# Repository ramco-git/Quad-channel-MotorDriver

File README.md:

# クアッドチャンネルモータードライバ (超はんだもりもり森鴎外!）

クアッドチャネルのDCブラシ付きモータードライバ基板です。内臓MCUにSTM32F405RGT6を使用し、4つのエンコーダ入力と1つのUART、1つのclassic CANに対応しています。内部でのPID制御が可能です。エンコーダはインクリメンタル式にのみ対応し、ゼロ校正に必要なZ相を引き出しています。すべての通信線は5Vトレラントピンに接続されています。入力信号をダイオードによりミックスしているため、内部から、又は外部から直接PWMとDIR信号を入力して動作させることができます。

## 仕様
・MCUにSTM32F405RGT6を使用し、回転数、位置制御を基板単体で可能です。
| 機能 | 個数 | 備考 |
|-:|-|-|
| モータードライバ | 4 | 30V、連続10A(なお性能試験を行っていないため、詳細は不明) |
| モーター出力 | 4 | XT60PW-F |
| 電源入力 | 1 | XT60PW-M |
|　MCU | 1 | STM32F405RGT6 |
| ユーザーLED | 1 | RGBの一体型チップ |
| ユーザーボタン | 1 | CANのID設定などに使用 |

## 信号線、マイコンのピンアサイン、コネクタの種類、番号
 
| 機能 | ピン | コネクタ種類 | パッドナンバー | 備考 |
|-:|-|-|-|-|
| CAN | TX(PB9) RX(PB8) | S04B-XASK-1,B04B-XASK-1 | J18,J19 | 
| UART | TX(PB10) RX(PB11) | DF1BZ-4P-2.5DSA | J6 |
| エンコーダ-1 | A(PA8) B(PA9) Z(PC0) | S05B-PASK-2 | J1 | TIM1 |
| エンコーダ-2 | A(PA0) B(PA1) Z(PC1) | S05B-PASK-2 | J2 | TIM2 |
| エンコーダ-3 | A(PA6) B(PA7) Z(PC2) | S05B-PASK-2 | J3 | TIM3 |
| エンコーダ-4 | A(PB6) B(PB7) Z(PC3) | S05B-PASK-2 | J4 | TIM4 |
| PWM-1(内臓MCUから) | PWM(PC6) DIR(PB12) | - | - | TIM8-CH1 |
| PWM-2(内臓MCUから) | PWM(PC7) DIR(PB13) | - | - | TIM8-CH2 |
| PWM-3(内臓MCUから) | PWM(PC8) DIR(PA10) | - | - | TIM8-CH3 |
| PWM-4(内臓MCUから) | PWM(PC9) DIR(PA11) | - | - | TIM8-CH4 |
| PWM-1(外部入力から) | DIR(1ピン) PWM(2ピン) GND(3ピン) | B03B-XASK-1 | J14 | - |
| PWM-2(外部入力から) | DIR(1ピン) PWM(2ピン) GND(3ピン) | B03B-XASK-1 | J15 | - |
| PWM-3(外部入力から) | DIR(1ピン) PWM(2ピン) GND(3ピン) | B03B-XASK-1 | J16 | - |
| PWM-4(外部入力から) | DIR(1ピン) PWM(2ピン) GND(3ピン) | B03B-XASK-1 | J17 | - |
| マイコン電源入力 | 12V(未使用,1ピン) 5V(2ピン) GND(3ピン) | B3B-XH-A | J7 | - |
| ユーザーLED | 赤(PB14) 緑(PA3) 青(PB15) | | D2 | TIMに接続されている |
| ユーザーボタン | (PC15) | - | SW2 | - | マイコン側でプルアップする |

## 内部ファームウェア
・現在調整中です。しばらくお待ちください。

## 名前の由来
大電流に対応させるため、銅線をバスバーとして使用した。その結果、基板がはんだだらけになってしまった。「超」はんだもりもり森鷗外!が誕生した。

## 以前の問題
・PWM,DIR信号ミックスに使用したBAT54CTのフットプリントのサイズミス
・部品番号の煩雑性

公開版では改善されています。

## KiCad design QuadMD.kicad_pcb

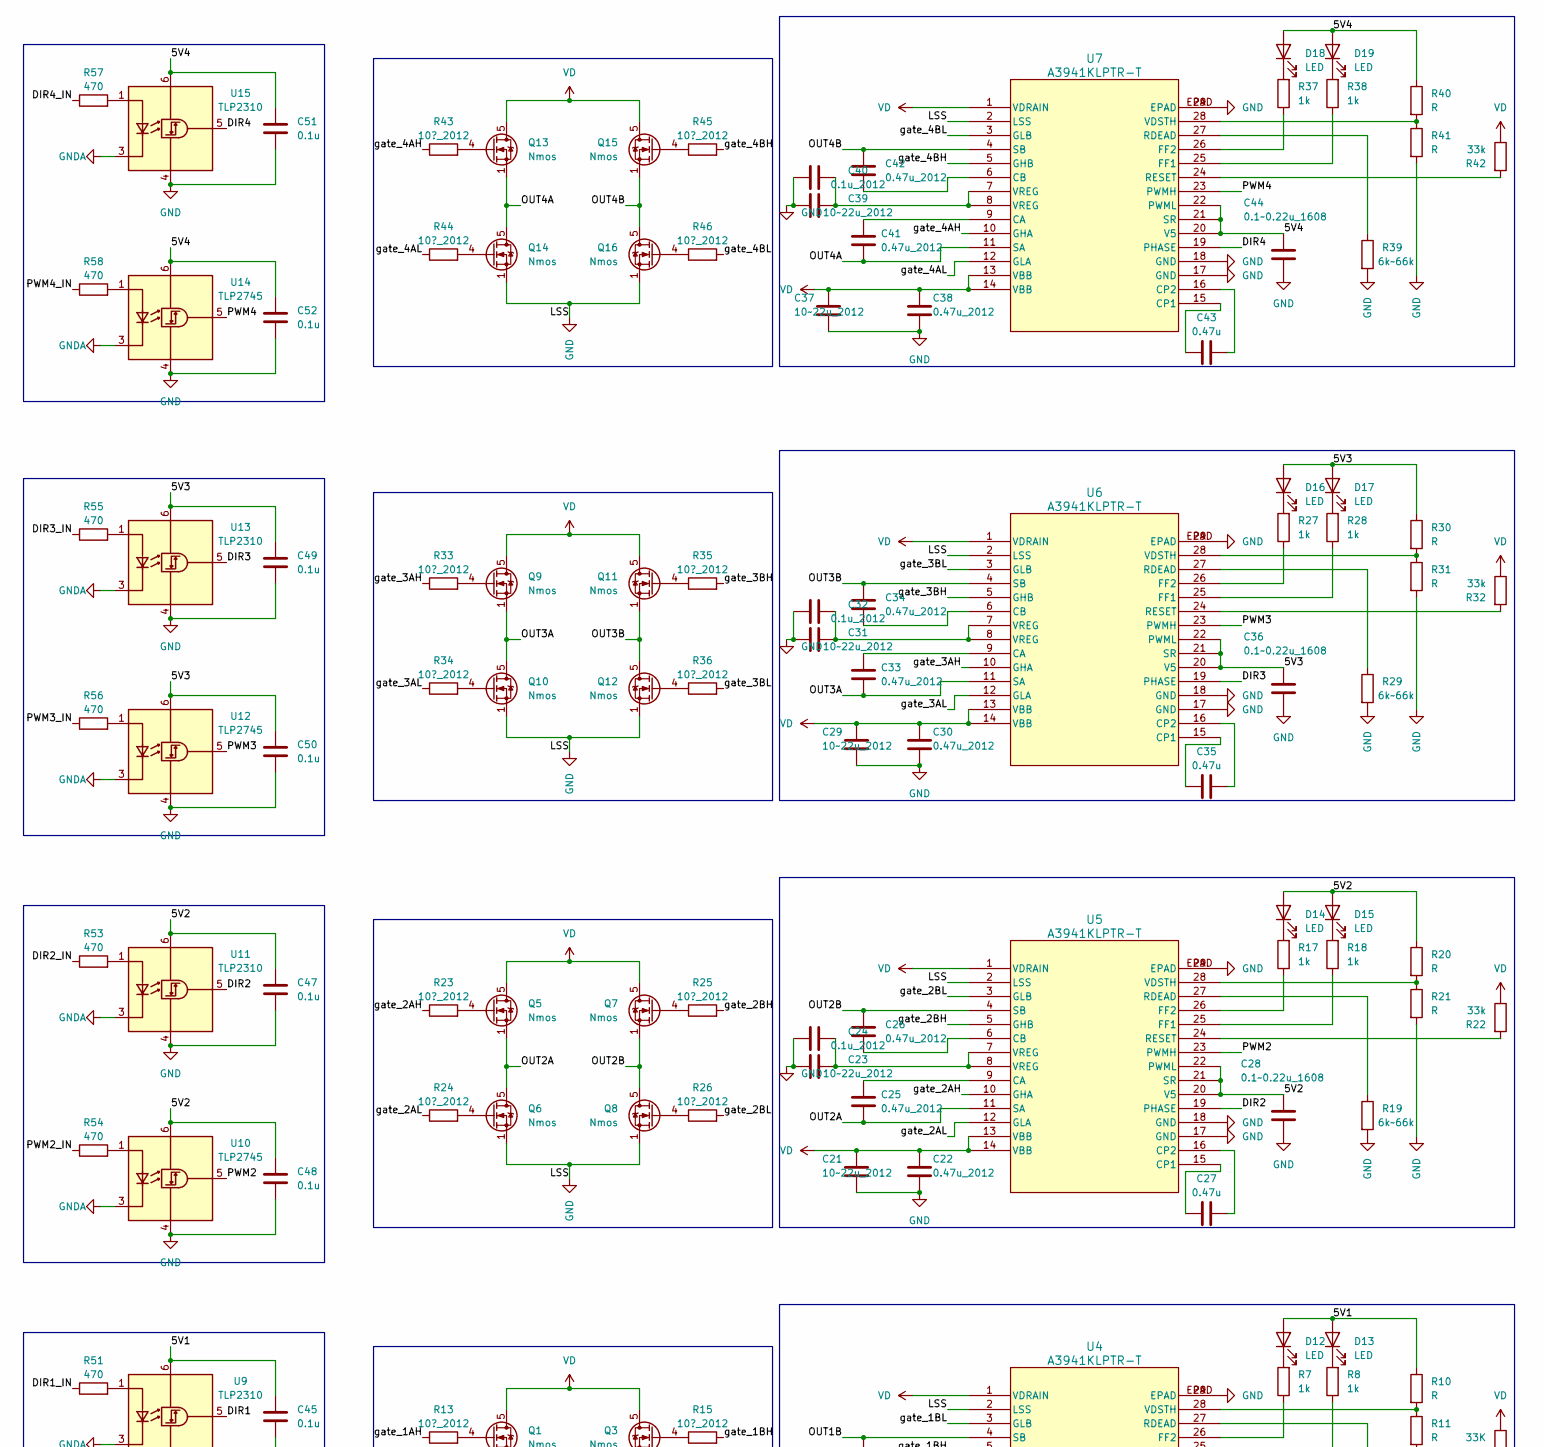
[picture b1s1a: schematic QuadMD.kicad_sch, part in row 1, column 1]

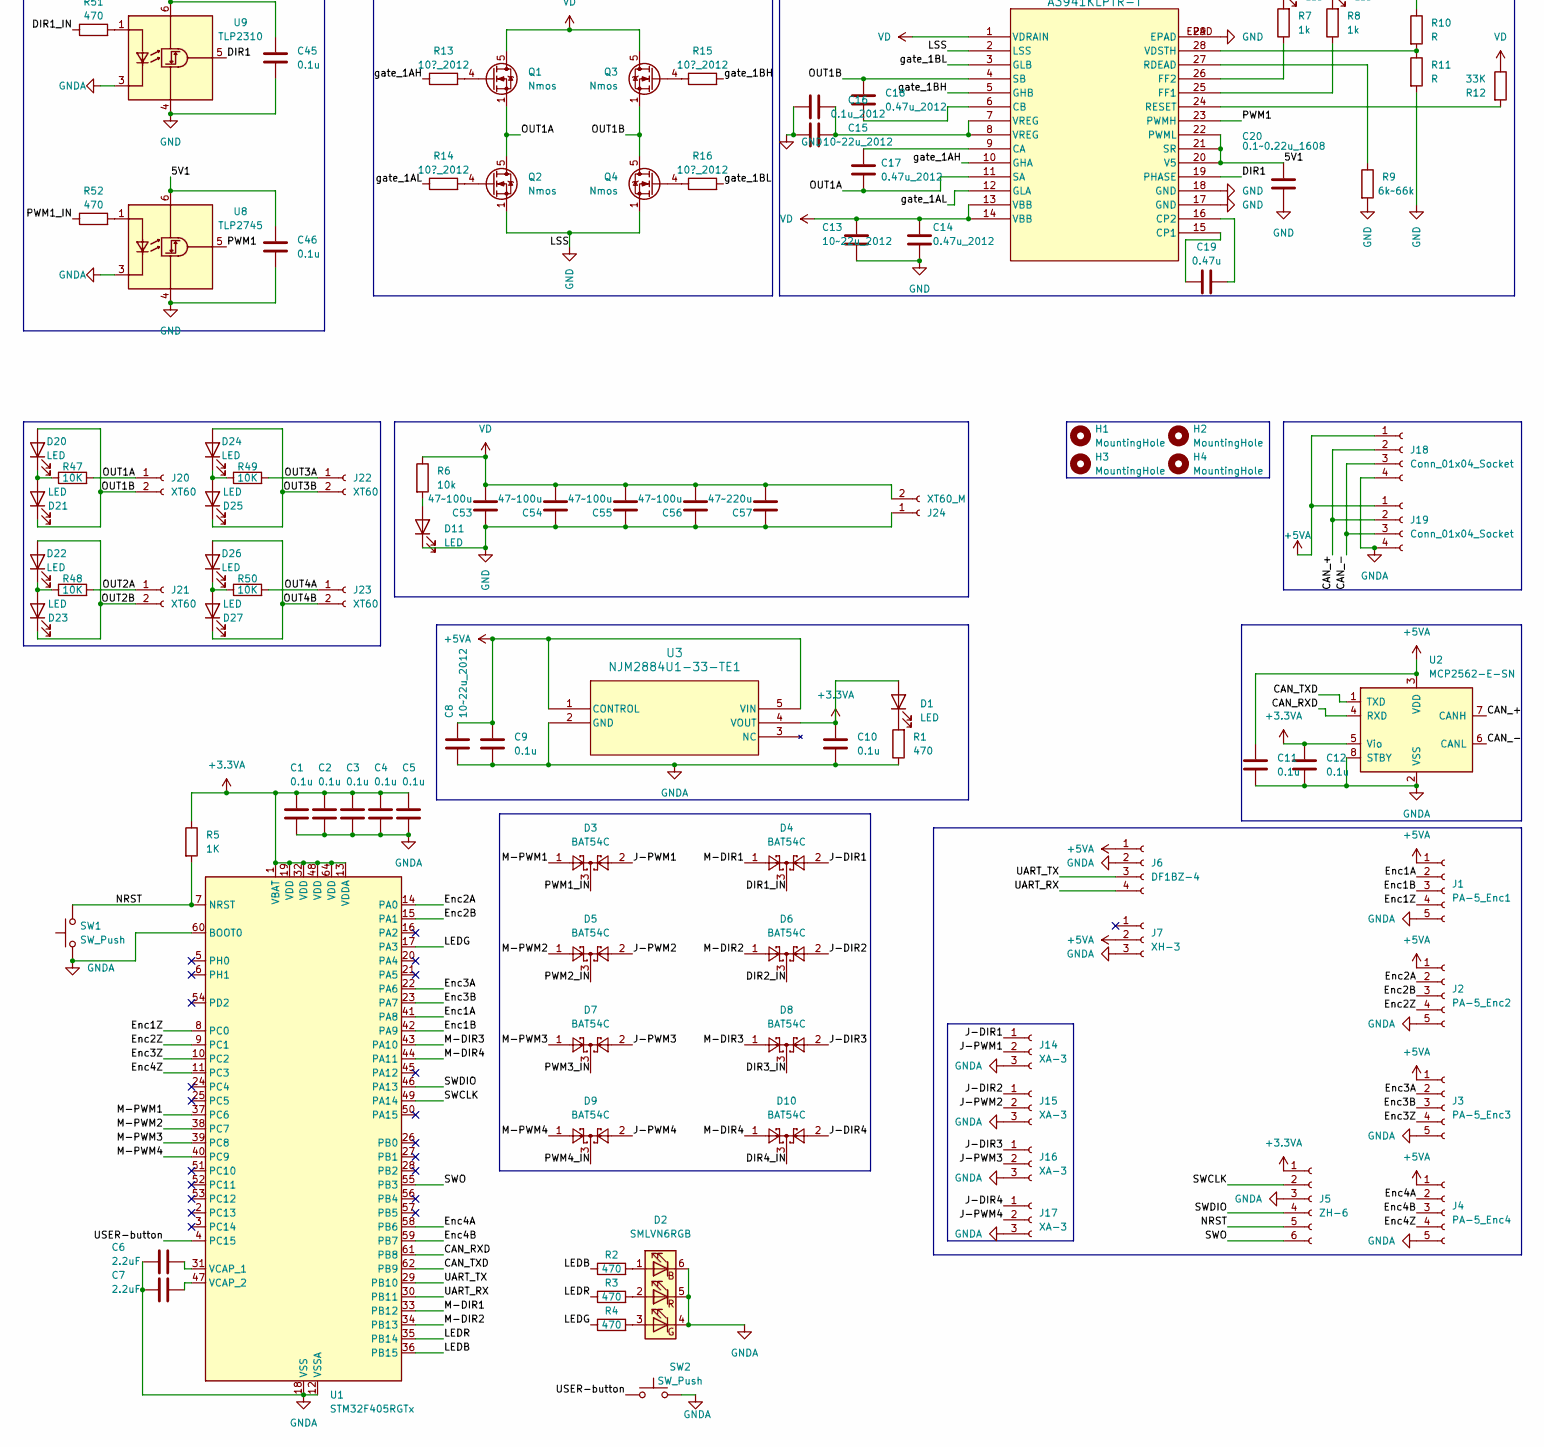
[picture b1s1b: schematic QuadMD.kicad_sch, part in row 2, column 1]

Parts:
C1, C2, C3, C4, C5, C9, C10, C11, C12, C45, C46, C47, C48, C49, C50, C51, C52: 0.1u; C_0603_1608Metric
C6, C7: 2.2uF; C_0603_1608Metric
C8, C13, C15, C21, C23, C29, C31, C37, C39: 10~22u_2012; C_0805_2012Metric
C14, C17, C18, C22, C25, C26, C30, C33, C34, C38, C41, C42: 0.47u_2012; C_0805_2012Metric
C16, C24, C32, C40: 0.1u_2012; C_0805_2012Metric
C19, C27, C35, C43: 0.47u; C_0805_2012Metric
C20, C28, C36, C44: 0.1~0.22u_1608; C_0603_1608Metric
C53, C54, C55, C56: 47~100u; CP_Elec_6.3x5.7
C57: 47~220u; CP_Elec_10x10.5
D1, D11, D12, D13, D14, D15, D16, D17, D18, D19: LED; LED_0603_1608Metric
D2: SMLVN6RGB; LED_ROHM_SMLVN6
D3, D4, D5, D6, D7, D8, D9, D10: BAT54C; SOT-523
D20, D21, D22, D23, D24, D25, D26, D27: LED; LED_0805_2012Metric
H1, H2, H3, H4: MountingHole; MountingHole_M3_FBMask
J1: PA-5_Enc1; CONN_S05B-PASK_PA_JST
J2: PA-5_Enc2; CONN_S05B-PASK_PA_JST
J3: PA-5_Enc3; CONN_S05B-PASK_PA_JST
J4: PA-5_Enc4; CONN_S05B-PASK_PA_JST
J5: ZH-6; JST_ZH_B6B-ZR_1x06_P1.50mm_Vertical
J6: DF1BZ-4; CON4_1X4_U_DF1BZ
J7: XH-3; JST_XH_B3B-XH-A_1x03_P2.50mm_Vertical
J14, J15, J16, J17: XA-3; JST_XA_B03B-XASK-1_1x03_P2.50mm_Vertical
J18: Conn_01x04_Socket; JST_XA_B04B-XASK-1_1x04_P2.50mm_Vertical
J19: Conn_01x04_Socket; JST_XA_S04B-XASK-1N-BN_1x04_P2.50mm_Horizontal
J20, J21, J22, J23: XT60; AMASS_XT60PW-F_1x02_P7.20mm_Horizontal
J24: XT60_M; AMASS_XT60PW-M_1x02_P7.20mm_Horizontal
Q1, Q2, Q3, Q4, Q5, Q6, Q7, Q8, Q9, Q10, Q11, Q12, Q13, Q14, Q15, Q16: Nmos; PQFN-8-EP_6x5mm_P1.27mm_Generic
R1, R2, R3, R4, R51, R52, R53, R54, R55, R56, R57, R58: 470; R_0603_1608Metric
R5: 1K; R_0603_1608Metric
R6: 10k; R_0603_1608Metric
R7, R8, R17, R18, R27, R28, R37, R38: 1k; R_0603_1608Metric
R9, R19, R29, R39: 6k~66k; R_0603_1608Metric
R10, R11, R20, R21, R30, R31, R40, R41: R; R_0603_1608Metric
R12: 33K; R_0603_1608Metric
R13, R14, R15, R16, R23, R24, R25, R26, R33, R34, R35, R36, R43, R44, R45, R46: 10?_2012; R_0805_2012Metric
R22, R32, R42: 33k; R_0603_1608Metric
R47, R48, R49, R50: 10K; R_0603_1608Metric
SW1, SW2: SW_Push; SW_Push_SPST_NO_Alps_SKRK
U1: STM32F405RGTx; LQFP-64_10x10mm_P0.5mm
U2: MCP2562-E-SN; SOIC-8_3.9x4.9mm_P1.27mm
U3: NJM2884U1-33-TE1; SOT-89-5
U4, U5, U6, U7: A3941KLPTR-T; TSSOP-28-PAD_TH
U8, U10, U12, U14: TLP2745; SO-6L_10x3.84mm_P1.27mm
U9, U11, U13, U15: TLP2310; SO-5-6_4.55x3.7mm_P1.27mm

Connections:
+3.3VA: C1.1, C2.1, C3.1, C4.1, C5.1, C10.1, C12.1, D1.2 (A), J5.1, R5.1, U1.1 (VBAT), U1.13 (VDDA), U1.19 (VDD), U1.32 (VDD), U1.48 (VDD), U1.64 (VDD), U2.5 (Vio), U3.4 (VOUT)
+5VA: C8.1, C9.1, C11.1, J1.1, J2.1, J3.1, J4.1, J6.1, J7.2, J18.1, J19.1, U2.3 (VDD), U3.1 (CONTROL), U3.5 (VIN)
/5V1: C20.2, C45.2, C46.2, D12.2 (A), D13.2 (A), R10.1, U4.20 (V5), U4.21 (SR), U4.22 (PWML), U8.6 (VDD), U9.6 (VDD)
/5V2: C28.2, C47.2, C48.2, D14.2 (A), D15.2 (A), R20.1, U5.20 (V5), U5.21 (SR), U5.22 (PWML), U10.6 (VDD), U11.6 (VDD)
/5V3: C36.2, C49.2, C50.2, D16.2 (A), D17.2 (A), R30.1, U6.20 (V5), U6.21 (SR), U6.22 (PWML), U12.6 (VDD), U13.6 (VDD)
/5V4: C44.2, C51.2, C52.2, D18.2 (A), D19.2 (A), R40.1, U7.20 (V5), U7.21 (SR), U7.22 (PWML), U14.6 (VDD), U15.6 (VDD)
/CAN_+: J18.2, J19.2, U2.7 (CANH)
/CAN_-: J18.3, J19.3, U2.6 (CANL)
/CAN_RXD: U1.61 (PB8), U2.4 (RXD)
/CAN_TXD: U1.62 (PB9), U2.1 (TXD)
/DIR1: U4.19 (PHASE), U9.5 (VO)
/DIR1_IN: D4.3, R51.1
/DIR2: U5.19 (PHASE), U11.5 (VO)
/DIR2_IN: D6.3, R53.1
/DIR3: U6.19 (PHASE), U13.5 (VO)
/DIR3_IN: D8.3, R55.1
/DIR4: U7.19 (PHASE), U15.5 (VO)
/DIR4_IN: D10.3, R57.1
/Enc1A: J1.2, U1.41 (PA8)
/Enc1B: J1.3, U1.42 (PA9)
/Enc1Z: J1.4, U1.8 (PC0)
/Enc2A: J2.2, U1.14 (PA0)
/Enc2B: J2.3, U1.15 (PA1)
/Enc2Z: J2.4, U1.9 (PC1)
/Enc3A: J3.2, U1.22 (PA6)
/Enc3B: J3.3, U1.23 (PA7)
/Enc3Z: J3.4, U1.10 (PC2)
/Enc4A: J4.2, U1.58 (PB6)
/Enc4B: J4.3, U1.59 (PB7)
/Enc4Z: J4.4, U1.11 (PC3)
/J-DIR1: D4.2, J14.1
/J-DIR2: D6.2, J15.1
/J-DIR3: D8.2, J16.1
/J-DIR4: D10.2, J17.1
/J-PWM1: D3.2, J14.2
/J-PWM2: D5.2, J15.2
/J-PWM3: D7.2, J16.2
/J-PWM4: D9.2, J17.2
/LEDB: R2.1, U1.36 (PB15)
/LEDG: R4.1, U1.17 (PA3)
/LEDR: R3.1, U1.35 (PB14)
/M-DIR1: D4.1, U1.33 (PB12)
/M-DIR2: D6.1, U1.34 (PB13)
/M-DIR3: D8.1, U1.43 (PA10)
/M-DIR4: D10.1, U1.44 (PA11)
/M-PWM1: D3.1, U1.37 (PC6)
/M-PWM2: D5.1, U1.38 (PC7)
/M-PWM3: D7.1, U1.39 (PC8)
/M-PWM4: D9.1, U1.40 (PC9)
/NRST: J5.5, R5.2, SW1.2, U1.7 (NRST)
/OUT1A: C17.1, J20.1, Q1.1 (S), Q1.2 (S), Q1.3 (S), Q2.5 (D), R47.2, U4.11 (SA)
/OUT1B: C18.2, D20.2 (A), D21.1 (K), J20.2, Q3.1 (S), Q3.2 (S), Q3.3 (S), Q4.5 (D), U4.4 (SB)
/OUT2A: C25.1, J21.1, Q5.1 (S), Q5.2 (S), Q5.3 (S), Q6.5 (D), R48.2, U5.11 (SA)
/OUT2B: C26.2, D22.2 (A), D23.1 (K), J21.2, Q7.1 (S), Q7.2 (S), Q7.3 (S), Q8.5 (D), U5.4 (SB)
/OUT3A: C33.1, J22.1, Q9.1 (S), Q9.2 (S), Q9.3 (S), Q10.5 (D), R49.2, U6.11 (SA)
/OUT3B: C34.2, D24.2 (A), D25.1 (K), J22.2, Q11.1 (S), Q11.2 (S), Q11.3 (S), Q12.5 (D), U6.4 (SB)
/OUT4A: C41.1, J23.1, Q13.1 (S), Q13.2 (S), Q13.3 (S), Q14.5 (D), R50.2, U7.11 (SA)
/OUT4B: C42.2, D26.2 (A), D27.1 (K), J23.2, Q15.1 (S), Q15.2 (S), Q15.3 (S), Q16.5 (D), U7.4 (SB)
/PWM1: U4.23 (PWMH), U8.5 (VO)
/PWM1_IN: D3.3, R52.1
/PWM2: U5.23 (PWMH), U10.5 (VO)
/PWM2_IN: D5.3, R54.1
/PWM3: U6.23 (PWMH), U12.5 (VO)
/PWM3_IN: D7.3, R56.1
/PWM4: U7.23 (PWMH), U14.5 (VO)
/PWM4_IN: D9.3, R58.1
/SWCLK: J5.2, U1.49 (PA14)
/SWDIO: J5.4, U1.46 (PA13)
/SWO: J5.6, U1.55 (PB3)
/UART_RX: J6.4, U1.30 (PB11)
/UART_TX: J6.3, U1.29 (PB10)
/USER-button: SW2.1, U1.4 (PC15)
/gate_1AH: R13.1, U4.10 (GHA)
/gate_1AL: R14.1, U4.12 (GLA)
/gate_1BH: R15.2, U4.5 (GHB)
/gate_1BL: R16.2, U4.3 (GLB)
/gate_2AH: R23.1, U5.10 (GHA)
/gate_2AL: R24.1, U5.12 (GLA)
/gate_2BH: R25.2, U5.5 (GHB)
/gate_2BL: R26.2, U5.3 (GLB)
/gate_3AH: R33.1, U6.10 (GHA)
/gate_3AL: R34.1, U6.12 (GLA)
/gate_3BH: R35.2, U6.5 (GHB)
/gate_3BL: R36.2, U6.3 (GLB)
/gate_4AH: R43.1, U7.10 (GHA)
/gate_4AL: R44.1, U7.12 (GLA)
/gate_4BH: R45.2, U7.5 (GHB)
/gate_4BL: R46.2, U7.3 (GLB)
GND: C13.2, C14.2, C15.1, C16.1, C20.1, C21.2, C22.2, C23.1, C24.1, C28.1, C29.2, C30.2, C31.1, C32.1, C36.1, C37.2, C38.2, C39.1, C40.1, C44.1, C45.1, C46.1, C47.1, C48.1, C49.1, C50.1, C51.1, C52.1, C53.2, C54.2, C55.2, C56.2, C57.2, D11.1 (K), J24.1, Q2.1 (S), Q2.2 (S), Q2.3 (S), Q4.1 (S), Q4.2 (S), Q4.3 (S), Q6.1 (S), Q6.2 (S), Q6.3 (S), Q8.1 (S), Q8.2 (S), Q8.3 (S), Q10.1 (S), Q10.2 (S), Q10.3 (S), Q12.1 (S), Q12.2 (S), Q12.3 (S), Q14.1 (S), Q14.2 (S), Q14.3 (S), Q16.1 (S), Q16.2 (S), Q16.3 (S), R9.2, R11.2, R19.2, R21.2, R29.2, R31.2, R39.2, R41.2, U4.2 (LSS), U4.17 (GND), U4.18 (GND), U4.29 (EPAD), U4.EPAD, U5.2 (LSS), U5.17 (GND), U5.18 (GND), U5.29 (EPAD), U5.EPAD, U6.2 (LSS), U6.17 (GND), U6.18 (GND), U6.29 (EPAD), U6.EPAD, U7.2 (LSS), U7.17 (GND), U7.18 (GND), U7.29 (EPAD), U7.EPAD, U8.4 (GND), U9.4 (GND), U10.4 (GND), U11.4 (GND), U12.4 (GND), U13.4 (GND), U14.4 (GND), U15.4 (GND)
GNDA: C1.2, C2.2, C3.2, C4.2, C5.2, C6.1, C7.1, C8.2, C9.2, C10.2, C11.2, C12.2, D2.4 (GK), D2.5 (RK), D2.6 (BK), J1.5, J2.5, J3.5, J4.5, J5.3, J6.2, J7.3, J14.3, J15.3, J16.3, J17.3, J18.4, J19.4, R1.1, SW1.1, SW2.2, U1.12 (VSSA), U1.18 (VSS), U1.60 (BOOT0), U1.63 (VSS), U2.2 (VSS), U2.8 (STBY), U3.2 (GND), U8.3 (K), U9.3 (K), U10.3 (K), U11.3 (K), U12.3 (K), U13.3 (K), U14.3 (K), U15.3 (K)
unnamed: C15.2, C16.2, U4.7 (VREG), U4.8 (VREG)
unnamed: C23.2, C24.2, U5.7 (VREG), U5.8 (VREG)
unnamed: C31.2, C32.2, U6.7 (VREG), U6.8 (VREG)
unnamed: C39.2, C40.2, U7.7 (VREG), U7.8 (VREG)
unnamed: D1.1 (K), R1.2
unnamed: D2.1 (BA), R2.2
unnamed: D2.3 (GA), R4.2
unnamed: D2.2 (RA), R3.2
unnamed: D11.2 (A), R6.2
unnamed: D12.1 (K), R7.2
unnamed: D13.1 (K), R8.2
unnamed: D14.1 (K), R17.2
unnamed: D15.1 (K), R18.2
unnamed: D16.1 (K), R27.2
unnamed: D17.1 (K), R28.2
unnamed: D18.1 (K), R37.2
unnamed: D19.1 (K), R38.2
unnamed: D20.1 (K), D21.2 (A), R47.1
unnamed: D22.1 (K), D23.2 (A), R48.1
unnamed: D24.1 (K), D25.2 (A), R49.1
unnamed: D26.1 (K), D27.2 (A), R50.1
unnamed: Q1.4 (G), R13.2
unnamed: Q2.4 (G), R14.2
unnamed: Q3.4 (G), R15.1
unnamed: Q4.4 (G), R16.1
unnamed: Q5.4 (G), R23.2
unnamed: Q6.4 (G), R24.2
unnamed: Q7.4 (G), R25.1
unnamed: Q8.4 (G), R26.1
unnamed: Q9.4 (G), R33.2
unnamed: Q10.4 (G), R34.2
unnamed: Q11.4 (G), R35.1
unnamed: Q12.4 (G), R36.1
unnamed: Q13.4 (G), R43.2
unnamed: Q14.4 (G), R44.2
unnamed: Q15.4 (G), R45.1
unnamed: Q16.4 (G), R46.1
unnamed: C6.2, U1.31 (VCAP_1)
unnamed: C7.2, U1.47 (VCAP_2)
unnamed: C17.2, U4.9 (CA)
unnamed: C18.1, U4.6 (CB)
unnamed: C19.1, U4.15 (CP1)
unnamed: C19.2, U4.16 (CP2)
unnamed: R8.1, U4.25 (FF1)
unnamed: R7.1, U4.26 (FF2)
unnamed: R9.1, U4.27 (RDEAD)
unnamed: R12.2, U4.24 (RESET)
unnamed: R10.2, R11.1, U4.28 (VDSTH)
unnamed: C25.2, U5.9 (CA)
unnamed: C26.1, U5.6 (CB)
unnamed: C27.1, U5.15 (CP1)
unnamed: C27.2, U5.16 (CP2)
unnamed: R18.1, U5.25 (FF1)
unnamed: R17.1, U5.26 (FF2)
unnamed: R19.1, U5.27 (RDEAD)
unnamed: R22.2, U5.24 (RESET)
unnamed: R20.2, R21.1, U5.28 (VDSTH)
unnamed: C33.2, U6.9 (CA)
unnamed: C34.1, U6.6 (CB)
unnamed: C35.1, U6.15 (CP1)
unnamed: C35.2, U6.16 (CP2)
unnamed: R28.1, U6.25 (FF1)
unnamed: R27.1, U6.26 (FF2)
unnamed: R29.1, U6.27 (RDEAD)
unnamed: R32.2, U6.24 (RESET)
unnamed: R30.2, R31.1, U6.28 (VDSTH)
unnamed: C41.2, U7.9 (CA)
unnamed: C42.1, U7.6 (CB)
unnamed: C43.1, U7.15 (CP1)
unnamed: C43.2, U7.16 (CP2)
unnamed: R38.1, U7.25 (FF1)
unnamed: R37.1, U7.26 (FF2)
unnamed: R39.1, U7.27 (RDEAD)
unnamed: R42.2, U7.24 (RESET)
unnamed: R40.2, R41.1, U7.28 (VDSTH)
unnamed: R52.2, U8.1 (A)
unnamed: R51.2, U9.1 (A)
unnamed: R54.2, U10.1 (A)
unnamed: R53.2, U11.1 (A)
unnamed: R56.2, U12.1 (A)
unnamed: R55.2, U13.1 (A)
unnamed: R58.2, U14.1 (A)
unnamed: R57.2, U15.1 (A)
VD: C13.1, C14.1, C21.1, C22.1, C29.1, C30.1, C37.1, C38.1, C53.1, C54.1, C55.1, C56.1, C57.1, J24.2, Q1.5 (D), Q3.5 (D), Q5.5 (D), Q7.5 (D), Q9.5 (D), Q11.5 (D), Q13.5 (D), Q15.5 (D), R6.1, R12.1, R22.1, R32.1, R42.1, U4.1 (VDRAIN), U4.13 (VBB), U4.14 (VBB), U5.1 (VDRAIN), U5.13 (VBB), U5.14 (VBB), U6.1 (VDRAIN), U6.13 (VBB), U6.14 (VBB), U7.1 (VDRAIN), U7.13 (VBB), U7.14 (VBB)

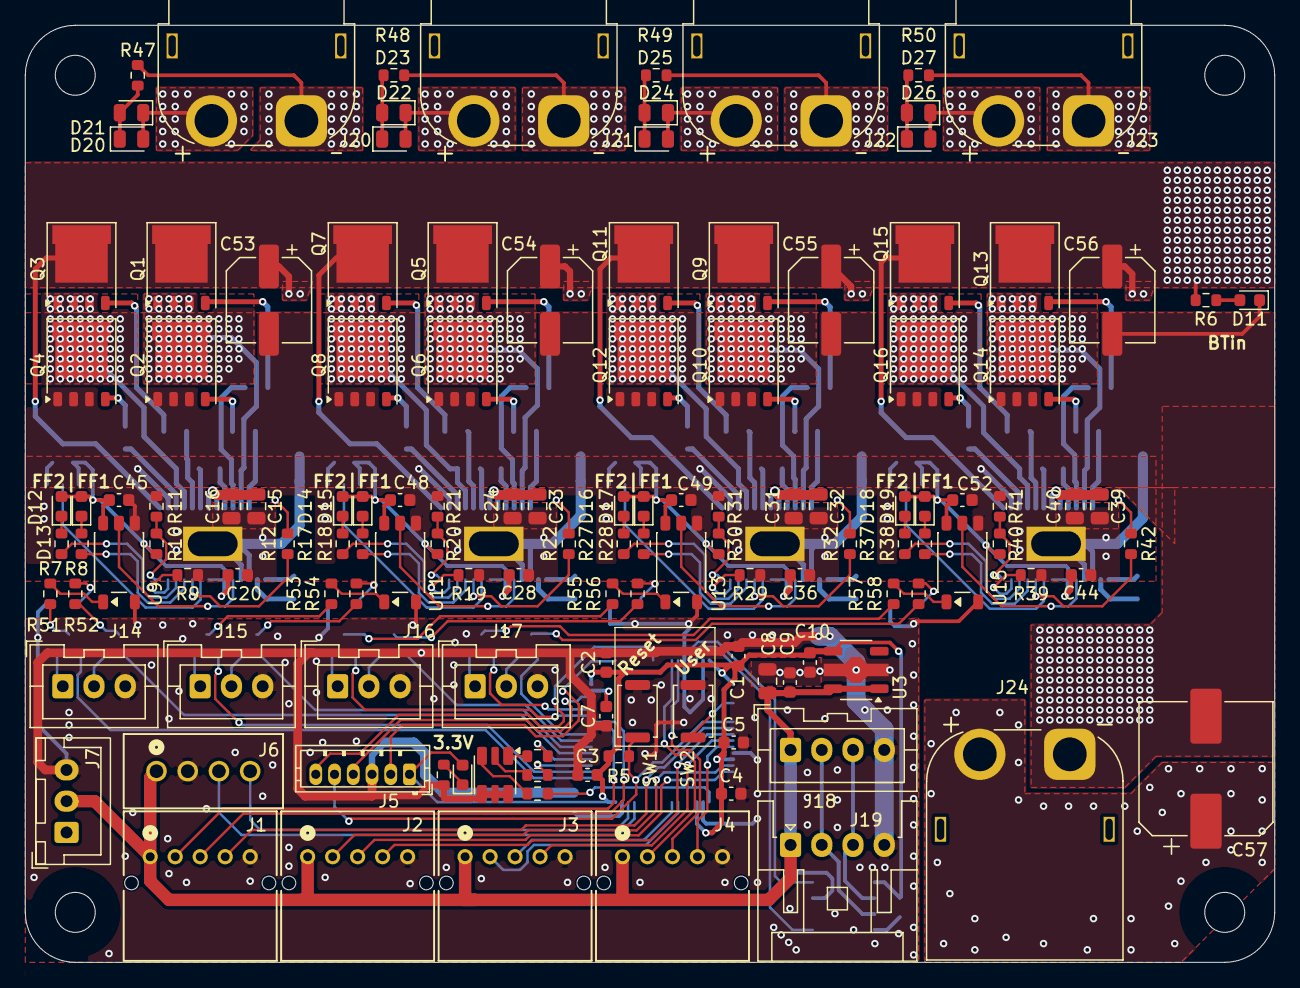
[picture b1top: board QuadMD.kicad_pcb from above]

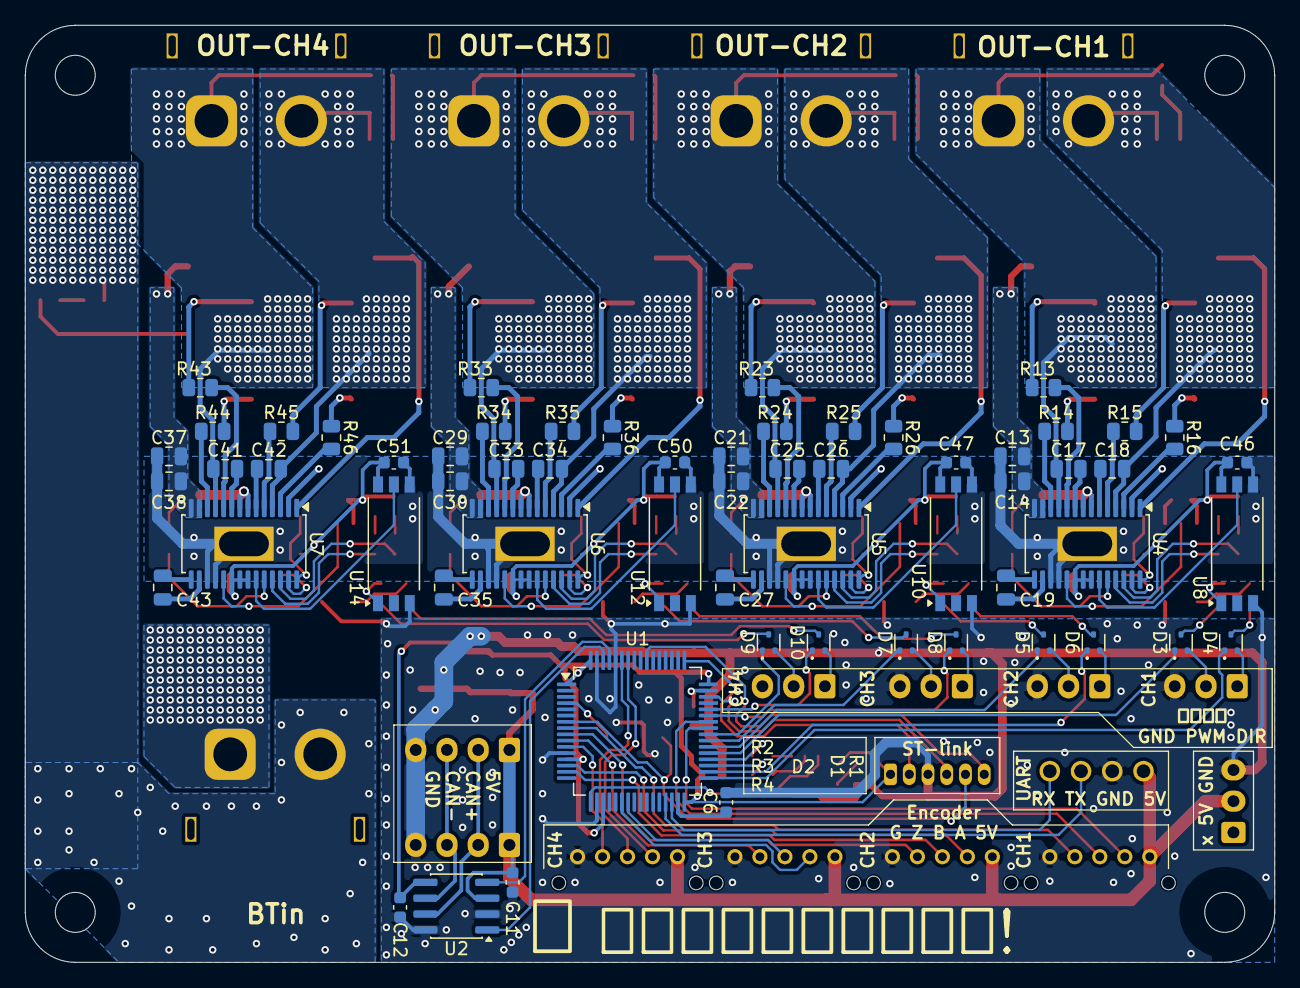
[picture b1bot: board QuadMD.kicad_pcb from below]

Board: 2 copper layers, 100.0 x 75.0 mm, 197 parts (61 on the bottom side), 174 nets.
